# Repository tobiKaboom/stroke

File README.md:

# stroke
> [!WARNING]
> i literally forgot to make the firmware lmao

> [!TIP]
> If you want to make this keyboard, i would advise you to use the money you would spend on this to go to therapy.

# concept
the original idea was a QAZ with bruce-like column stagger, but due to the nature of geometry itself its hard to use both staggers at once. therefore, it has a lot of gaps.
i also forgot to properly make the column stagger on both sides so the left is a bit lower than the right.
# reactions
the initial reactions were unanimous: this board is hideous.

> what the fuck is this
> 
> ethanbadmic

> WHAT THE ACTUAL FUCK IS GOING ON HERE??
>
> obabo

> this an the sinergy board are kinda goated tbh
>
> Anna

> it looks like you spilled a tray of keycaps. i love it
>
> calumwri

> !40s
>
> bibibuscotti

> What the actual fuck is this?
> 
>
> Dingusaurus Derp

> Why does it look like everything is tilted
>
> Starimmezzo

> 
> 
> mae

>ban him
>
>Joe Scotto

>That's Illegal
>
>Ruby

>Why is this kind of sick tho
>
>upset

>van ergogh lookin ahh
>
>kayso

>
>
>dashdashunderscoredash

# case
to add to the jankiness, you can of course just mount a pcb over the other and keep it as a sandwich, or use obabo's one, which is much better but not compatible because it requires a daughter board while i use an rp2040 zero, and i swear i cannot integrate circuits so i guess obabo's case is good if you want to handwire?

# disclaimer
this board has not been tested and i do not claim responsibility over any errors or malfunctions in the pcb, case, plate or any other component 

# license
This work falls under the Creative Commons Attribution-ShareAlike 4.0 international license. For more info, check LICENSE.md or https://creativecommons.org/licenses/by-sa/4.0/deed.en

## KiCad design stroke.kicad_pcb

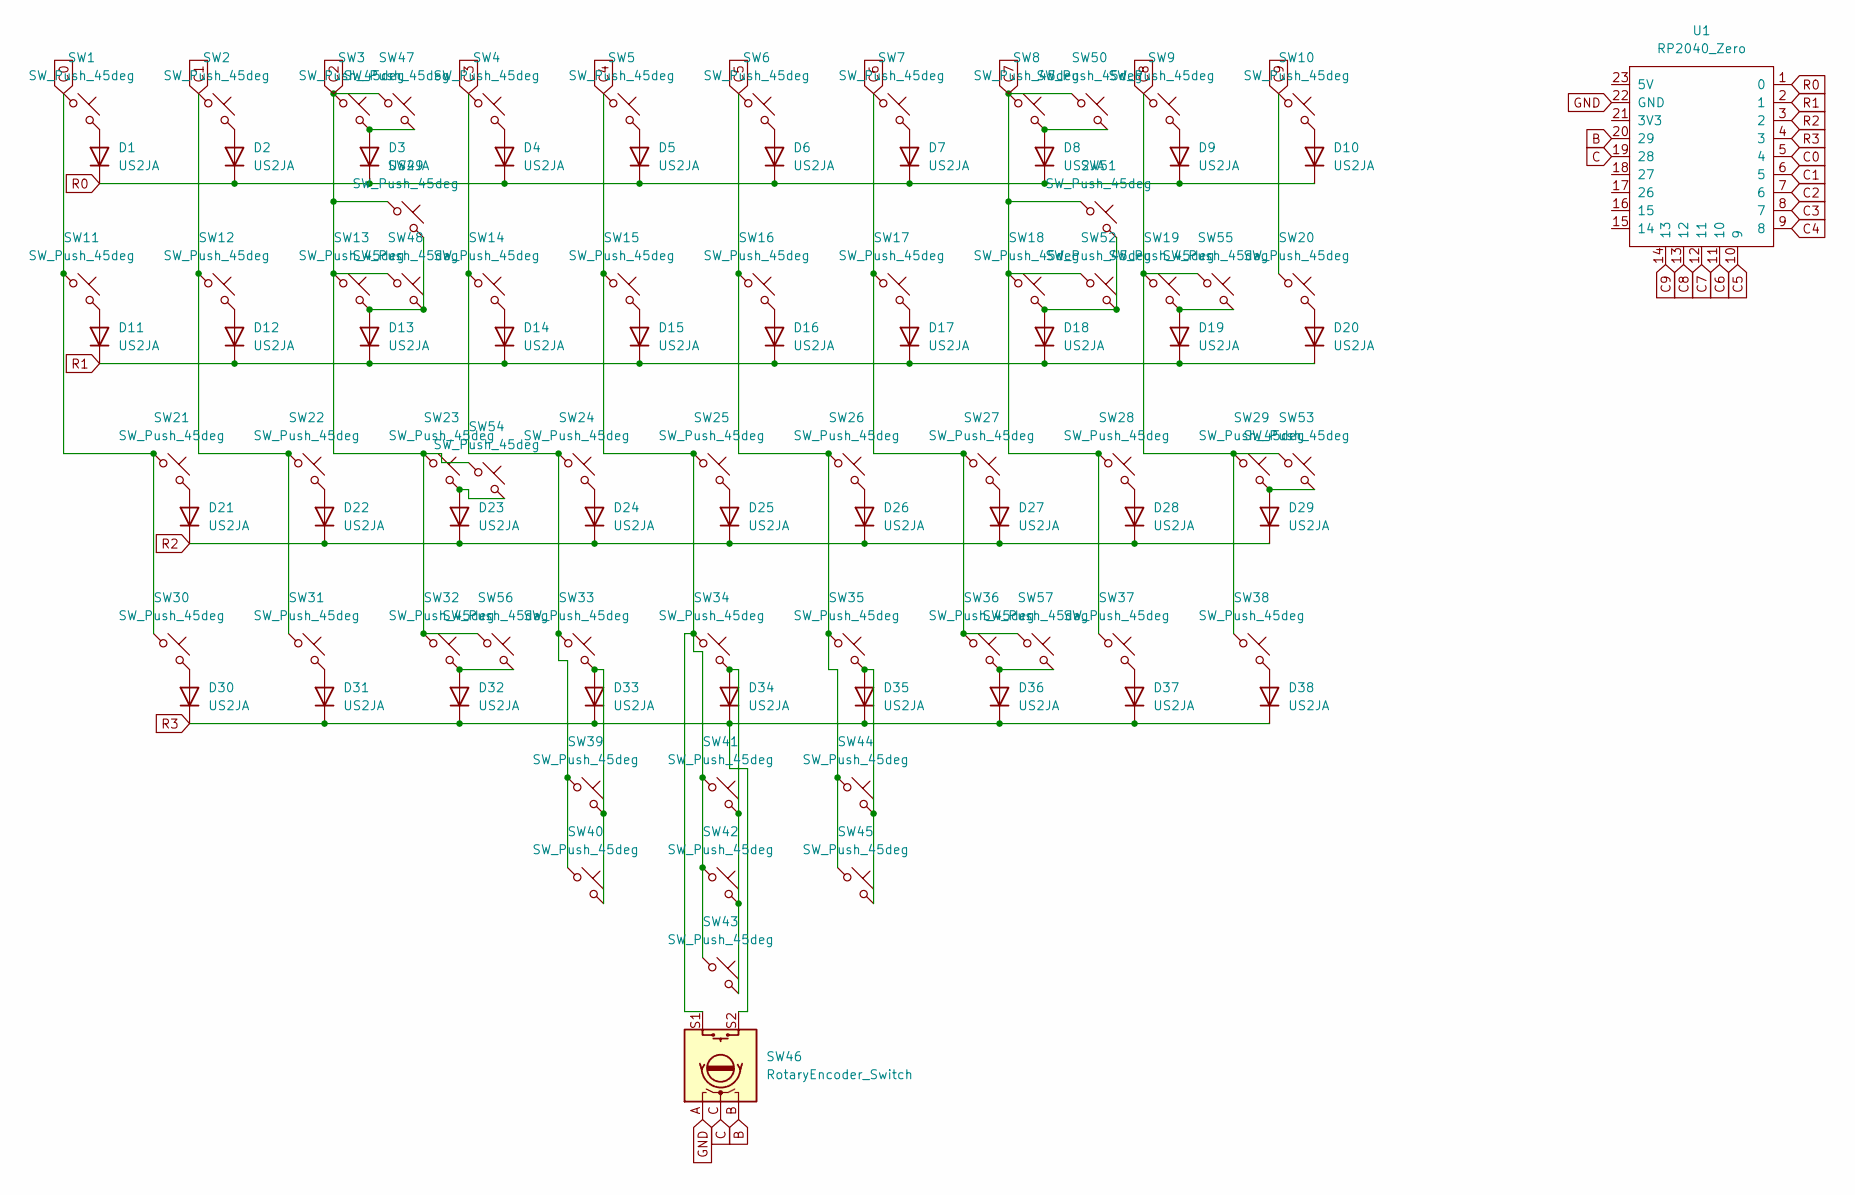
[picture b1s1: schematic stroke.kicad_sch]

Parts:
D1, D2, D3, D4, D5, D6, D7, D8, D9, D10, D11, D12, D13, D14, D15, D16, D17, D18, D19, D20, D21, D22, D23, D24, D25, D26, D27, D28, D29, D30, D31, D32, D33, D34, D35, D36, D37, D38: US2JA; Diode_SOD-123
SW1, SW2, SW3, SW4, SW5, SW6, SW7, SW8, SW9, SW12, SW13, SW14, SW15, SW16, SW17, SW18, SW19, SW20, SW22, SW23, SW24, SW25, SW26, SW27, SW28, SW30, SW31, SW32, SW36, SW37, SW38, SW41, SW42, SW43: SW_Push_45deg; MX_PCB_1.00u
SW10, SW11, SW48, SW52: SW_Push_45deg; MX_PCB_1.25u
SW21, SW39, SW44: SW_Push_45deg; MX_PCB_1.75u
SW29, SW47, SW50: SW_Push_45deg; MX_PCB_1.50u
SW33, SW35: SW_Push_45deg; MX_PCB_2.75u
SW34, SW53: SW_Push_45deg; MX_PCB_2.00u
SW40, SW45: SW_Push_45deg; MX_PCB_2.25u
SW46: RotaryEncoder_Switch; RotaryEncoder_Alps_EC11E-Switch_Vertical_H20mm
SW49, SW51: SW_Push_45deg; MX_PCB_ISOEnter
SW54, SW55, SW56: SW_Push_45deg; MX_PCB_1.25u_90deg
SW57: SW_Push_45deg; MX_PCB_1.50u_90deg
U1: RP2040_Zero; RP2040_Zero_Flipped

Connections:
B: SW46.B, U1.20 (29)
C: SW46.C, U1.19 (28)
C0: SW1.1, SW11.1, SW21.1, SW30.1, U1.5 (4)
C1: SW2.1, SW12.1, SW22.1, SW31.1, U1.6 (5)
C2: SW3.1, SW13.1, SW23.1, SW32.1, SW47.1, SW48.1, SW49.1, SW54.1, SW56.1, U1.7 (6)
C3: SW4.1, SW14.1, SW24.1, SW33.1, SW39.1, SW40.1, U1.8 (7)
C4: SW5.1, SW15.1, SW25.1, SW34.1, SW41.1, SW42.1, SW43.1, SW46.S1, U1.9 (8)
C5: SW6.1, SW16.1, SW26.1, SW35.1, SW44.1, SW45.1, U1.10 (9)
C6: SW7.1, SW17.1, SW27.1, SW36.1, SW57.1, U1.11 (10)
C7: SW8.1, SW18.1, SW28.1, SW37.1, SW50.1, SW51.1, SW52.1, U1.12 (11)
C8: SW9.1, SW19.1, SW29.1, SW38.1, SW53.1, SW55.1, U1.13 (12)
C9: SW10.1, SW20.1, U1.14 (13)
GND: SW46.A, U1.22 (GND)
unnamed: D1.2 (A), SW1.2
unnamed: D2.2 (A), SW2.2
unnamed: D3.2 (A), SW3.2, SW47.2
unnamed: D4.2 (A), SW4.2
unnamed: D5.2 (A), SW5.2
unnamed: D6.2 (A), SW6.2
unnamed: D7.2 (A), SW7.2
unnamed: D8.2 (A), SW8.2, SW50.2
unnamed: D9.2 (A), SW9.2
unnamed: D10.2 (A), SW10.2
unnamed: D11.2 (A), SW11.2
unnamed: D12.2 (A), SW12.2
unnamed: D13.2 (A), SW13.2, SW48.2, SW49.2
unnamed: D14.2 (A), SW14.2
unnamed: D15.2 (A), SW15.2
unnamed: D16.2 (A), SW16.2
unnamed: D17.2 (A), SW17.2
unnamed: D18.2 (A), SW18.2, SW51.2, SW52.2
unnamed: D19.2 (A), SW19.2, SW55.2
unnamed: D20.2 (A), SW20.2
unnamed: D21.2 (A), SW21.2
unnamed: D22.2 (A), SW22.2
unnamed: D23.2 (A), SW23.2, SW54.2
unnamed: D24.2 (A), SW24.2
unnamed: D25.2 (A), SW25.2
unnamed: D26.2 (A), SW26.2
unnamed: D27.2 (A), SW27.2
unnamed: D28.2 (A), SW28.2
unnamed: D29.2 (A), SW29.2, SW53.2
unnamed: D30.2 (A), SW30.2
unnamed: D31.2 (A), SW31.2
unnamed: D32.2 (A), SW32.2, SW56.2
unnamed: D33.2 (A), SW33.2, SW39.2, SW40.2
unnamed: D34.2 (A), SW34.2, SW41.2, SW42.2, SW43.2
unnamed: D35.2 (A), SW35.2, SW44.2, SW45.2
unnamed: D36.2 (A), SW36.2, SW57.2
unnamed: D37.2 (A), SW37.2
unnamed: D38.2 (A), SW38.2
R0: D1.1 (K), D2.1 (K), D3.1 (K), D4.1 (K), D5.1 (K), D6.1 (K), D7.1 (K), D8.1 (K), D9.1 (K), D10.1 (K), U1.1 (0)
R1: D11.1 (K), D12.1 (K), D13.1 (K), D14.1 (K), D15.1 (K), D16.1 (K), D17.1 (K), D18.1 (K), D19.1 (K), D20.1 (K), U1.2 (1)
R2: D21.1 (K), D22.1 (K), D23.1 (K), D24.1 (K), D25.1 (K), D26.1 (K), D27.1 (K), D28.1 (K), D29.1 (K), U1.3 (2)
R3: D30.1 (K), D31.1 (K), D32.1 (K), D33.1 (K), D34.1 (K), D35.1 (K), D36.1 (K), D37.1 (K), D38.1 (K), SW46.S2, U1.4 (3)

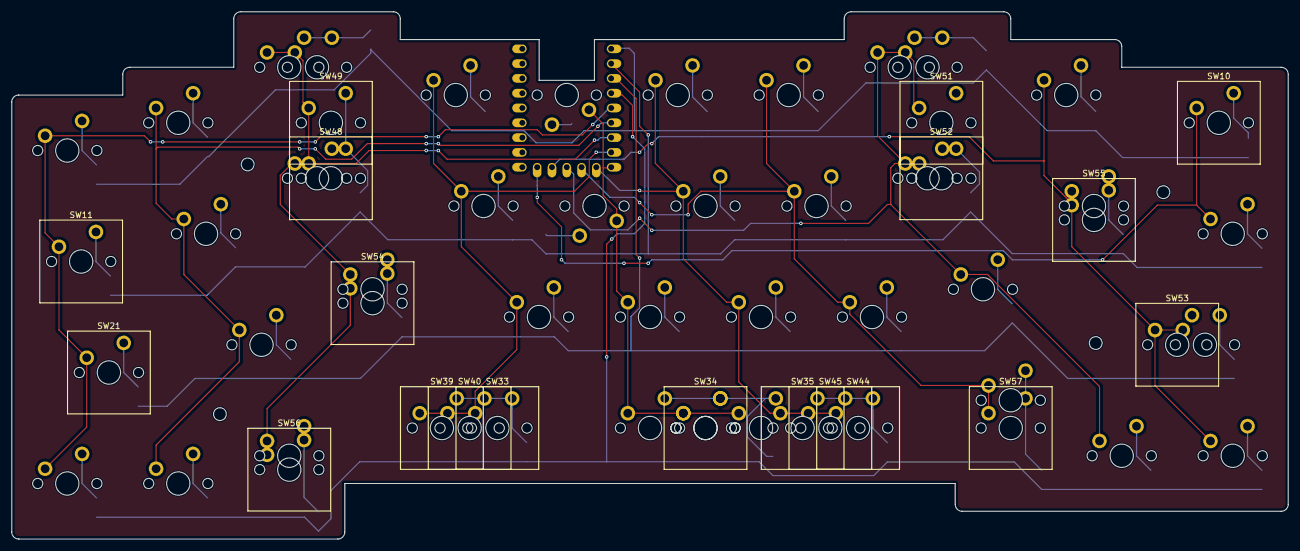
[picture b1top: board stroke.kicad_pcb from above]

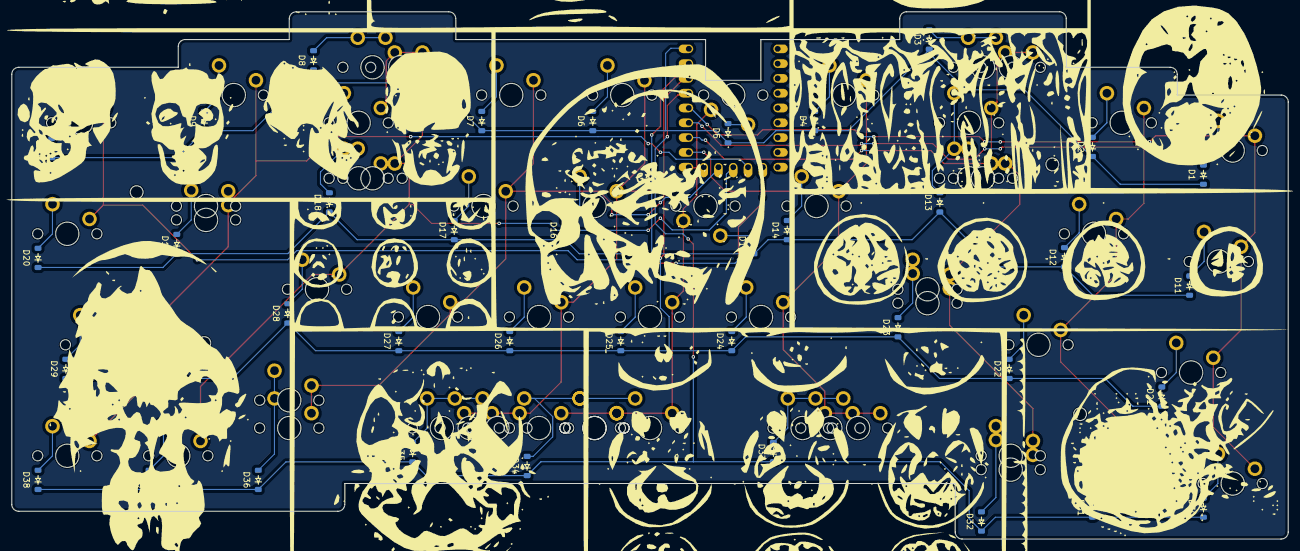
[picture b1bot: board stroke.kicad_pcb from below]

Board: 2 copper layers, 219.0 x 90.4 mm, 95 parts (39 on the bottom side), 52 nets.

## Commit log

2024-07-13 Rename CC-BY-SA.md to LICENSE.md
2025-02-10 added quotes to readme
